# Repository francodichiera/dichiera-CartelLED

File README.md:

# Cartel LED inteligente Proyecto Final 2025
###

<table align="center">
  <tr>
    <td></td>
    <td></td>
  </tr>
</table>

###
## 
- Proyecto: cartel LED multiplexado controlado por ESP32, columnas por 3×74HC595 (24 cols), filas por transistores TIP122.
(POR CADA MODULO).

- EL CARTEL CUENTA CON 18 FILAS x 96 COLUMNAS (4 MODULOS CONECTADOS HORIZONTALMENTE).

- CON UNAS DIMENSIONES DE LA ESTRUCTURA DE: 1.7m x 40cm.

## Agradecimientos

Antes de pasar a la explicacion, quiero agradecer especialmente al **Prof. Ing. Facundo Luzko** por su importante ayuda y guía en la programación del cartel, al **Prof. Ricardo Malvasio** por su valiosa orientación y colaboración durante el desarrollo del proyecto, y a **mi viejo**, por su apoyo incondicional en todo momento.

# Resumen

Este repositorio contiene el firmware para un cartel LED multiplexado con ESP32. Usa 3 registros 74HC595 en cascada para controlar 24 columnas y 18 pines del ESP32 (a través de transistores TIP122 o drivers) para seleccionar filas. El microcontrolador corre un servidor web simple que permite enviar el texto que se desplaza horizontalmente (scroll), elegir dirección y velocidad y persiste la configuración en flash con `Preferences`.

# Características

-   Matriz: `MATRIX_ROWS = 18`, `MATRIX_COLS = 24` (configurable).
    
-   Control de columnas por 3×`74HC595` en cascada.
    
-   Control de filas por pines del ESP32 (transistores TIP122 u otro driver).
    
-   Framebuffer en RAM: `framebuffer[MATRIX_ROWS][BYTES_PER_ROW]`.
    
-   Librería gráfica `Adafruit_GFX` + fuente compilada.
    
-   Interfaz web responsive para editar el mensaje, ver demo y ajustar velocidad/dirección.
    
-   Persistencia con `Preferences` (mensaje, velocidad, dirección).
    
-   mDNS disponible: `cartelhuergo.local` (si mDNS funciona en tu red).

----------

# Diagrama y conexionado (detalle)

> **Nota importante:** el ejemplo asume columnas manejadas por 74HC595 como _fuente_ (HIGH = +V para anodos) y filas controladas por NPN (TIP122) que _conectan a GND_ (sink) cuando activadas. Esta es la configuración que coincide con el comportamiento del código (`sr.set(b, HIGH)` y `digitalWrite(filas[f], HIGH)` para activar fila).

### Conexiones básicas

Señales principales (ESP32 ↔ 74HC595)

- DATA_PIN (23) -> Serial Data (DS / SER) del primer 74HC595

- CLOCK_PIN (18) -> Shift clock (SH_CP)

- LATCH_PIN (19) -> Store clock / latch (ST_CP)

### Salidas 74HC595 -> columnas

-   Q0..Q7 (primer registro) -> columnas 0..7
    
-   Q0..Q7 (segundo registro) -> columnas 8..15
    
-   Q0..Q7 (tercer registro) -> columnas 16..23

Asegurate del orden físico: la librería / código usa `sr.set(b, value)` con `b` de 0 a 23. Si tus registros están conectados en distinto orden, reordena o ajusta mapping.

### Filas (por TIP122)

Cada fila física (catodo común en el esquema) va a un TIP122 que tiene:

-   Colector -> pin fila (panel LED)
    
-   Emisor -> GND
    
-   Base -> pin ESP32 a través de resistencia de 1k  
    En el código `digitalWrite(filas[f], HIGH)` activa la fila (enciende transistor, conecta a GND).

### Alimentación

-   **Fuente**: calcula la corriente por LED (Iled) × cantidad máxima encendida simultáneamente. En multiplexado de filas, una sola fila se enciende a la vez, por lo que la corriente máxima es (#LEDsPorFila × Iled). Ejemplo: 24 LEDs por fila × 20 mA = 480 mA por fila (añadir margen). Para 18 filas multiplexadas no sumes todas; la fuente debe poder suministrar el pico por fila y la electrónica.
    
-   **Voltage registers**: 74HC595 soporta Vcc 2–6V; si usas LED de 5V considera 5V lógica o usar nivel shifters. Con ESP32 (3.3V) se suele usar 5V para LEDs y la salida del 74HC595 a 5V está OK si los 74HC595 toleran 3.3V en entradas. Revisa datasheets o usa versiones 74HCT (más compatible con 3.3V).
    
-   GND común obligatorio.

----------

# Cómo funciona (conceptos clave)

1.  **Framebuffer**: `uint8_t framebuffer[MATRIX_ROWS][BYTES_PER_ROW];`
    
    -   Cada fila tiene `BYTES_PER_ROW` bytes (3) → 24 columnas → 24 bits por fila.
        
    -   El bit más significativo (0x80) corresponde a la columna `x % 8 == 0` por el cálculo `0x80 >> (x % 8)`.
        
2.  **Dibujo**: Heredas `Adafruit_GFX` con `MatrixDisplay` y sobreescribes `drawPixel(x,y,color)`. Cuando se escribe texto con `display.print(curMessage)` Adafruit_GFX setea pixels en el framebuffer.
    
3.  **Multiplexado**:
    
    -   `refrescarMatrizCompleta()` recorre filas `f = 0..MATRIX_ROWS-1`.
        
    -   Para cada fila: apaga fila previa, envía todos los 24 bits (columnas) al `74HC595` con `sr.set(b, ...)`, activa la fila actual (`prenderFila(f)`), espera `delayMicroseconds(100)` y la apaga.
        
    -   Los LEDs que deben estar on durante esa fila se encienden porque sus columnas están `HIGH` (desde el 74HC595) y la fila está siendo _sink_ por el TIP122.
        
4.  **Scroll**:
    
    -   `xPos` controla la posición horizontal; cada `scrollSpeed` ms el texto avanza `±1`.
        
    -   `display.getTextBounds()` calcula anchura `w` del texto para resetear `xPos`.
        
5.  **Web**:
    
    -   Un web server simple en puerto 80 sirve `WebPage` y procesa parámetros en URL `?MSG=...&SD=L|R&SP=xxx`.
        
    -   El código parsea URL en `getData()` decodificando `%xx`.
        
6.  **Persistencia**:
    
    -   `Preferences` guarda `mensaje`, `speed`, `dir` para restaurar tras reset.

----------

## Explicación técnica: ¿qué es y cómo funciona un TIP122?

**TIP122 — resumen práctico**

-   El TIP122 es un transistor Darlington NPN empaquetado (dos transistores en cascada dentro de un solo encapsulado).
    
-   Ventaja: **ganancia de corriente muy alta** (β muy grande), por eso con poca corriente de base podés conmutar corrientes relativamente altas en el colector.
    
-   Desventaja: **alta caída de saturación** (VCE(sat) típicamente ~1.5–2.5 V dependiendo de corriente), lo que produce **pérdida de potencia** y calor. Además la caída base-emisor de la entrada es mayor (~2.5–3V total, por las dos uniones).

**Cómo se usa en el cartel**

-   Usamos TIP122 como _sink_ por fila: cuando su base recibe HIGH, el transistor conecta la fila a GND permitiendo que los LEDs de esa fila con columna HIGH se iluminen.
    
-   Colocá **una resistencia en la base** entre ESP32 y la base del TIP122 (ej. 1kΩ es una buena práctica). Esto limita la corriente desde el pin del ESP32.

**Cálculos y precauciones**

-   Si `I_collector = 480 mA` y `VCEsat ≈ 2 V` → potencia en el transistor `P = VCEsat × I = 2 V × 0.48 A = 0.96 W`. Esto **genera calor** y normalmente requiere disipador.
    
-   Con ESP32 (GPIO a 3.3 V) la base del TIP122 queda con poca tensión sobre la resistencia (Vbase ≈ 2.5 V), por eso la corriente de base es pequeña — aun así la ganancia Darlington suele permitir conmutar la corriente del colector.
    
-   **Recomendación:** para menor pérdida térmica y menor VCE(sat) usar un **MOSFET N-channel lógico (logic-level)** como alternativa — mucho menor VDS(on) y menos calor. Ej: si conseguís un MOSFET de canal N con Rds(on) bajo y que se active con 3.3 V (IRLZ44N no siempre es la mejor opción, buscá específicamente “logic-level MOSFET”), vas a reducir pérdidas térmicas.

**Valores orientativos**

-   Resistencia base típica: `1kΩ` (puede ajustarse entre 470Ω y 4.7kΩ según diseño).
    
-   Verifica disipación térmica y agrega disipador o cambialo por MOSFET si vas a manejar corrientes grandes.

----------

## Explicación técnica: ¿qué es y cómo funciona un 74HC595?

**74HC595 — resumen práctico**

-   Es un _registro de desplazamiento (shift register)_ con latch y 8 salidas paralelas (Q0..Q7).
    
-   Funcionalmente tiene dos registros internos:
    
    -   **Shift register**: donde se van desplazando los bits con cada pulso de reloj (SH_CP).
        
    -   **Storage register** (o latch register): se actualiza cuando se pulsea ST_CP (latch). De este modo podés enviar muchos bits sin que las salidas cambien hasta que hagas latch.
        
-   Señales principales:
    
    -   `SER` (DS): serial data in
        
    -   `SH_CP` (clock): desplaza un bit en el shift register al flanco activo
        
    -   `ST_CP` (latch): copia el contenido del shift register al storage register → las salidas cambian
        
    -   `Q0..Q7`: salidas paralelas
        
    -   `Q7'` (o Q7S/Q7') suele ser serial out para encadenar el siguiente 74HC595 (cascada)
        
    -   `OE` (Output Enable, activa low) y `MR` (Master Reset, activa low) controlan si las salidas están habilitadas o si el registro se resetea

**Por qué lo usamos**

-   Permite controlar **muchas columnas** con solo 3 pines del micro (data, clock, latch).
    
-   Con `Q7'` encadenás los registros y podés manejar 24 columnas en serie.

**Consejos de uso**

-   **Cargar todos los bits** (ej. 3 bytes) en el shift register con pulsos de clock y al final hacer un `latch` para actualizar las salidas en una operación atómica. Esto evita glitches.
    
-   `OE` lo podés usar para blanking rápido (si querés apagar todas las salidas momentáneamente).
    
-   `MR` te permite resetear las salidas (activo bajo).

**Limitaciones eléctricas importantes**

-   Los pines del 74HC595 no están pensados para conducir corrientes muy altas de forma sostenida. Aunque pueden entregar decenas de mA en condiciones cortas, **no es buena idea esperar 20–25 mA sostenidos por salida sin verificar la hoja de datos**.
    
-   En multiplexado, cada salida del 74HC595 típicamente solo alimenta un LED a la vez (por fila), lo que reduce la corriente sostenida por pin, pero **es crucial usar resistencias por LED** y mantener la corriente por pin dentro de límites razonables.
    
-   Para compatibilidad con **ESP32 (3.3 V)** se recomienda la versión **74HCT595** o comprobar que la lógica 74HC595 que uses interpreta 3.3 V como HIGH de forma fiable. `74HCT` suele aceptar 3.3 V como HIGH cuando la alimentación del chip es 5 V — aún así, revisar datasheets.

**Buenas prácticas**

-   Si necesitás más corriente o brillo, usar drivers especializados para LEDs (p. ej. registros con driver de corriente constante) o agregar transistores por columna si vas a exigir >10 mA por salida.
    
-   Si microcontrolador y 74HC595 comparten diferentes tensiones (3.3V vs 5V), considera conversión de niveles o usar 74HCT compatibles.

# Dependencias y preparación del entorno

-   **Placa:** ESP32 (seleccionar en Arduino IDE -> Board Manager).
    
-   **Librerías (instalar desde Library Manager / Git):**
    
    -   `ShiftRegister74HC595` (o la que uses; tu código ya referencia la plantilla `ShiftRegister74HC595<3>`).
        
    -   `Adafruit_GFX` (para la API gráfica).
        
    -   `ESPmDNS` (incluida con núcleo ESP32).
        
    -   `Preferences` (incluida).
        
    -   Fuente convertida a header: `LEMONMILK_Regular11pt7b` (como `Fonts/LEMONMILK_Regular11pt7b.h`). Para convertir TTF → Adafruit font: usar `truetype2gfx` o `fontconvert` (links en comentarios del código).
        
        > `https://rop.nl/truetype2gfx/ FONTS PAGE`

### Recomendaciones de configuración en Arduino IDE

-   Board: `ESP32 Dev Module` (o el modelo exacto)
    
-   Flash Frequency: 80 MHz
    
-   Upload Speed: 115200 o 921600 (según tu puerto)
    
-   Partition Scheme: default (si necesitas mucha NVS, ajustar)

----------

# Interfaz Web / API

-   Página principal (sirve `WebPage`) incluye demo y formulario.
    
-   **Enviar**: pulsa `Enviar` en la UI → hace `window.location='/?MSG='+msg+'&SD='+SD+'&SP='+SP`.
    
-   **Formato URL manual**:
    
    `http://<IP_DEL_ESP32>/?MSG=Tu%20mensaje%20aqui&SD=L&SP=100` 
    
    -   `MSG` = texto codificado en URL (máx 255 chars en tu buffer).
        
    -   `SD` = `L` (izquierda) o `R` (derecha).
        
    -   `SP` = velocidad (entero). En tu código `scrollSpeed` en ms.
        
-   **Demo**: la demo en el HTML hace scroll CSS/JS y usa fuente tipo LED (DotGothic16).

----------

# Configuraciones persistentes

-   Namespace `prefs.begin("cartel", false);`
    
-   Keys:
    
    -   `"mensaje"` (String)
        
    -   `"speed"` (uint)
        
    -   `"dir"` (bool)
        
-   Para resetear preferencias manualmente: puedes añadir un endpoint `/reset` que haga `prefs.clear()` o borrar desde código.

----------

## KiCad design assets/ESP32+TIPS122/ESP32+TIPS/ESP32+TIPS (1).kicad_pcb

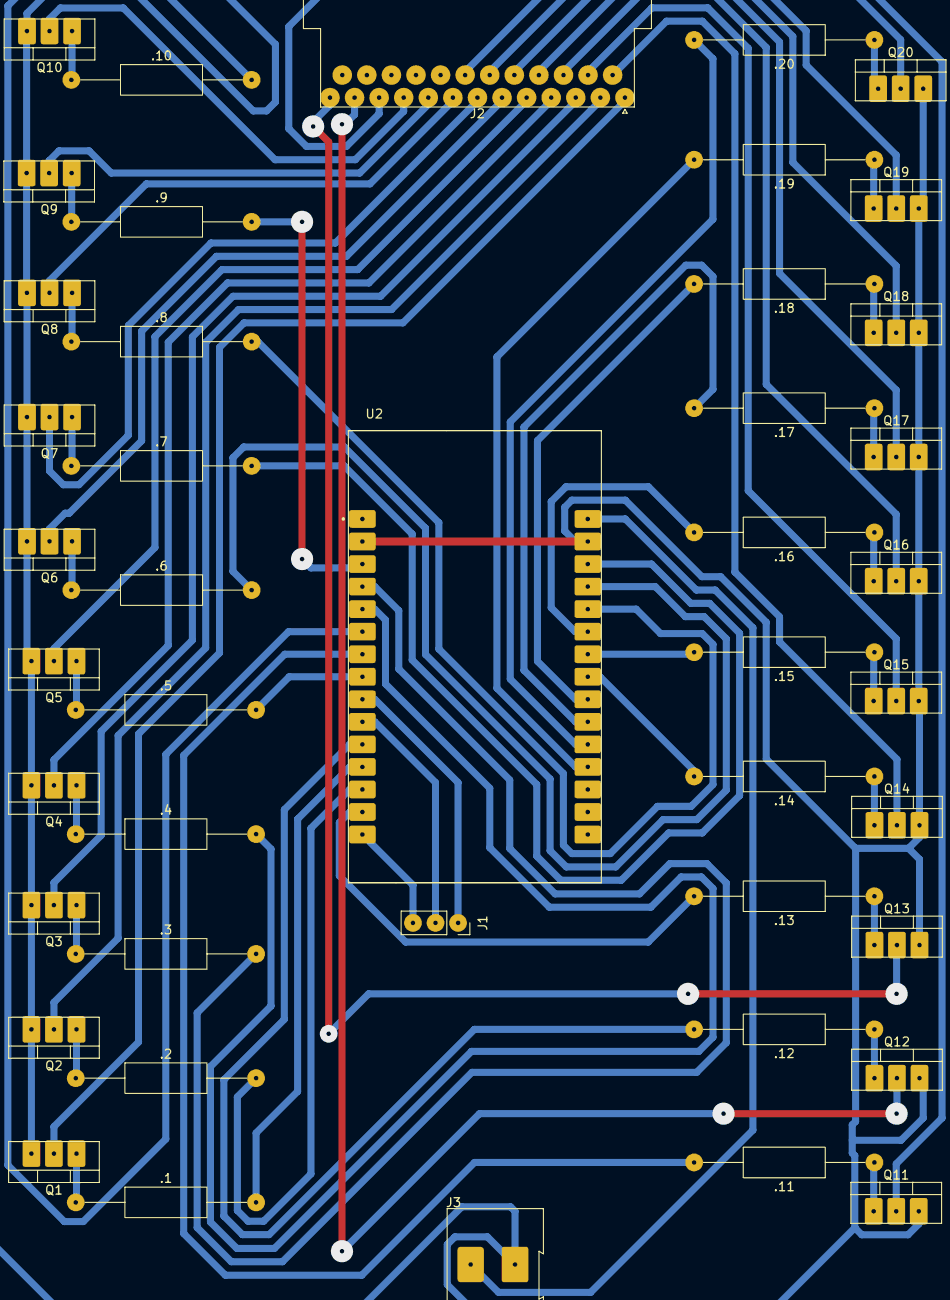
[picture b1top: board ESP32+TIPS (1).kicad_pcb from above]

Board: 2 copper layers, 44 parts (0 on the bottom side), 65 nets.

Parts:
.1, .2, .3, .4, .5, .6, .7, .8, .9, .10, .11, .12, .13, .14, .15, .16, .17, .18, .19, .20: 1K; R_Axial_DIN0309_L9.0mm_D3.2mm_P20.32mm_Horizontal
J1: Conn_01x03_Pin; PinSocket_1x03_P2.54mm_Vertical
J2: DB25_Socket; DSUB-25_Pins_Horizontal_P2.77x2.54mm_EdgePinOffset9.40mm
J3: Screw_Terminal_01x02; TerminalBlock_Altech_AK300-2_P5.00mm
Q1, Q2, Q3, Q4, Q5, Q6, Q7, Q8, Q9, Q10, Q11, Q12, Q13, Q14, Q15, Q16, Q17, Q18, Q19, Q20: TIP122; TO-220-3_Vertical
U2: ESP32-DEVKIT-V1; MODULE_ESP32_DEVKIT_V1

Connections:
GND: J3.2, Q1.3 (E), Q2.3 (E), Q3.3 (E), Q4.3 (E), Q5.3 (E), Q6.3 (E), Q7.3 (E), Q8.3 (E), Q9.3 (E), Q10.3 (E), Q11.3 (E), Q12.3 (E), Q13.3 (E), Q14.3 (E), Q15.3 (E), Q16.3 (E), Q17.3 (E), Q18.3 (E), Q19.3 (E), Q20.3 (E), U2.2 (GND), U2.29 (GND)
unnamed: J1.1, U2.9 (D18)
unnamed: J1.2, U2.10 (D19)
unnamed: J1.3, U2.15 (D23)
unnamed: J2.14, Q14.2 (C)
unnamed: J2.15, Q15.2 (C)
unnamed: J2.16, Q16.2 (C)
unnamed: J2.17, Q17.2 (C)
unnamed: J2.18, Q18.2 (C)
unnamed: J2.19, Q19.2 (C)
unnamed: J2.20, Q20.2 (C)
unnamed: .1.1, Q1.1 (B)
unnamed: J2.1, Q1.2 (C)
unnamed: .2.1, Q2.1 (B)
unnamed: J2.2, Q2.2 (C)
unnamed: .3.1, Q3.1 (B)
unnamed: J2.3, Q3.2 (C)
unnamed: .4.1, Q4.1 (B)
unnamed: J2.4, Q4.2 (C)
unnamed: .5.1, Q5.1 (B)
unnamed: J2.5, Q5.2 (C)
unnamed: .6.1, Q6.1 (B)
unnamed: J2.6, Q6.2 (C)
unnamed: .7.1, Q7.1 (B)
unnamed: J2.7, Q7.2 (C)
unnamed: .8.1, Q8.1 (B)
unnamed: J2.8, Q8.2 (C)
unnamed: .9.1, Q9.1 (B)
unnamed: J2.9, Q9.2 (C)
unnamed: .10.1, Q10.1 (B)
unnamed: J2.10, Q10.2 (C)
unnamed: .11.1, Q11.1 (B)
unnamed: J2.11, Q11.2 (C)
unnamed: .12.1, Q12.1 (B)
unnamed: J2.12, Q12.2 (C)
unnamed: .13.1, Q13.1 (B)
unnamed: J2.13, Q13.2 (C)
unnamed: .14.1, Q14.1 (B)
unnamed: .15.1, Q15.1 (B)
unnamed: .16.1, Q16.1 (B)
unnamed: .17.1, Q17.1 (B)
unnamed: .18.1, Q18.1 (B)
unnamed: .19.1, Q19.1 (B)
unnamed: .20.1, Q20.1 (B)
unnamed: .3.2, U2.4 (D2)
unnamed: .4.2, U2.5 (D4)
unnamed: .5.2, U2.8 (D5)
unnamed: .6.2, U2.27 (D12)
unnamed: .7.2, U2.28 (D13)
unnamed: .8.2, U2.26 (D14)
unnamed: .9.2, U2.3 (D15)
unnamed: .12.2, U2.11 (D21)
unnamed: .13.2, U2.14 (D22)
unnamed: .14.2, U2.23 (D25)
unnamed: .15.2, U2.24 (D26)
unnamed: .16.2, U2.25 (D27)
unnamed: .17.2, U2.21 (D32)
unnamed: .18.2, U2.22 (D33)
unnamed: .19.2, U2.19 (D34)
unnamed: .20.2, U2.20 (D35)
unnamed: .1.2, U2.12 (RX0)
unnamed: .10.2, U2.6 (RX2)
unnamed: .2.2, U2.13 (TX0)
unnamed: .11.2, U2.7 (TX2)
VCC: J3.1, U2.30 (VIN)

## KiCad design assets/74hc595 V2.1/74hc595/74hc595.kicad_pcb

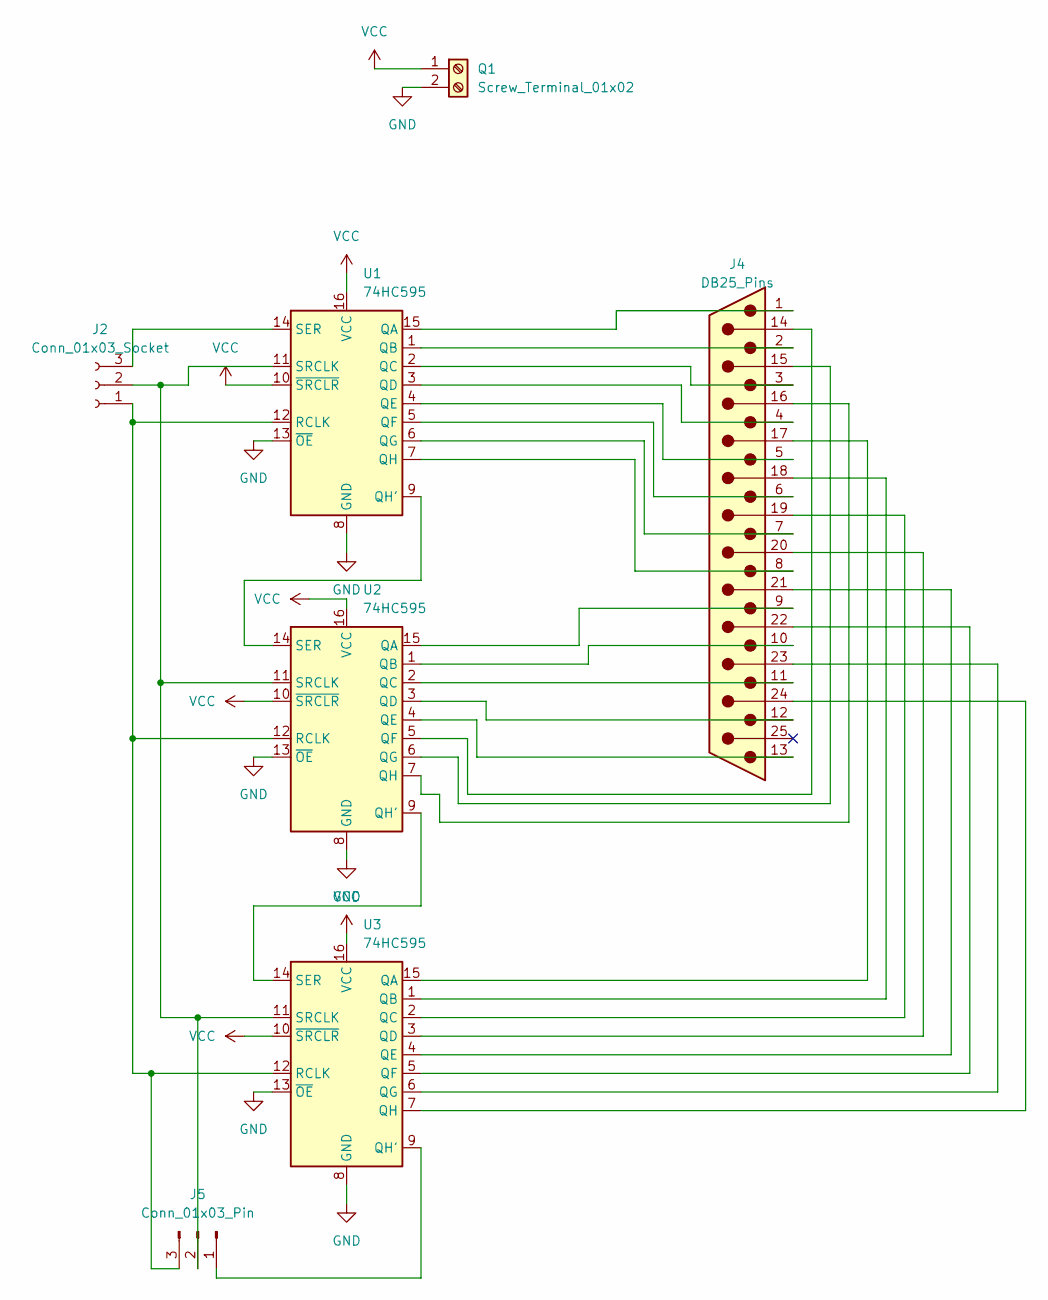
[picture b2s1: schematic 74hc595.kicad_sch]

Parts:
J2: Conn_01x03_Socket; PinHeader_1x03_P2.54mm_Vertical
J4: DB25_Pins; DSUB-25_Socket_Horizontal_P2.77x2.54mm_EdgePinOffset9.40mm
J5: Conn_01x03_Pin; PinHeader_1x03_P2.54mm_Vertical
Q1: Screw_Terminal_01x02; TerminalBlock_Altech_AK300-2_P5.00mm
U1, U2, U3: 74HC595; CERDIP-16_W7.62mm_SideBrazed_LongPads_Socket

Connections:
GND: Q1.2, U1.8 (GND), U1.13 (~OE), U2.8 (GND), U2.13 (~OE), U3.8 (GND), U3.13 (~OE)
unnamed: J2.1, J5.3, U1.12 (RCLK), U2.12 (RCLK), U3.12 (RCLK)
unnamed: J2.2, J5.2, U1.11 (SRCLK), U2.11 (SRCLK), U3.11 (SRCLK)
unnamed: J2.3, U1.14 (SER)
unnamed: J4.14, U2.5 (QF)
unnamed: J4.15, U2.6 (QG)
unnamed: J4.16, U2.7 (QH)
unnamed: J4.17, U3.15 (QA)
unnamed: J4.18, U3.1 (QB)
unnamed: J4.19, U3.2 (QC)
unnamed: J4.20, U3.3 (QD)
unnamed: J4.21, U3.4 (QE)
unnamed: J4.22, U3.5 (QF)
unnamed: J4.23, U3.6 (QG)
unnamed: J4.24, U3.7 (QH)
unnamed: J5.1, U3.9 (QH')
unnamed: J4.1, U1.15 (QA)
unnamed: J4.2, U1.1 (QB)
unnamed: J4.3, U1.2 (QC)
unnamed: J4.4, U1.3 (QD)
unnamed: J4.5, U1.4 (QE)
unnamed: J4.6, U1.5 (QF)
unnamed: J4.7, U1.6 (QG)
unnamed: U1.9 (QH'), U2.14 (SER)
unnamed: J4.8, U1.7 (QH)
unnamed: J4.9, U2.15 (QA)
unnamed: J4.10, U2.1 (QB)
unnamed: J4.11, U2.2 (QC)
unnamed: J4.12, U2.3 (QD)
unnamed: J4.13, U2.4 (QE)
unnamed: U2.9 (QH'), U3.14 (SER)
VCC: Q1.1, U1.10 (~SRCLR), U1.16 (VCC), U2.10 (~SRCLR), U2.16 (VCC), U3.10 (~SRCLR), U3.16 (VCC)

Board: 2 copper layers, 7 parts (0 on the bottom side), 32 nets, no tracks yet.

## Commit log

2025-08-06 agrego en code un archivo testing simplificado
2025-08-06 updates clase presencial (nueva libreria)
2025-08-07 agrego NuevaLib_matrix_Test
2025-08-07 attempt to turn on just one led
2025-08-08 update assets PCB
2025-08-08 update pcb
2025-08-10 Update para prender unico led
2025-08-12 update after matrix working
2025-08-28 update testingServer
2025-08-28 update fonts
2025-09-05 update refrezcarMatrizcompleta para mas registros
2025-10-08 finding the final
